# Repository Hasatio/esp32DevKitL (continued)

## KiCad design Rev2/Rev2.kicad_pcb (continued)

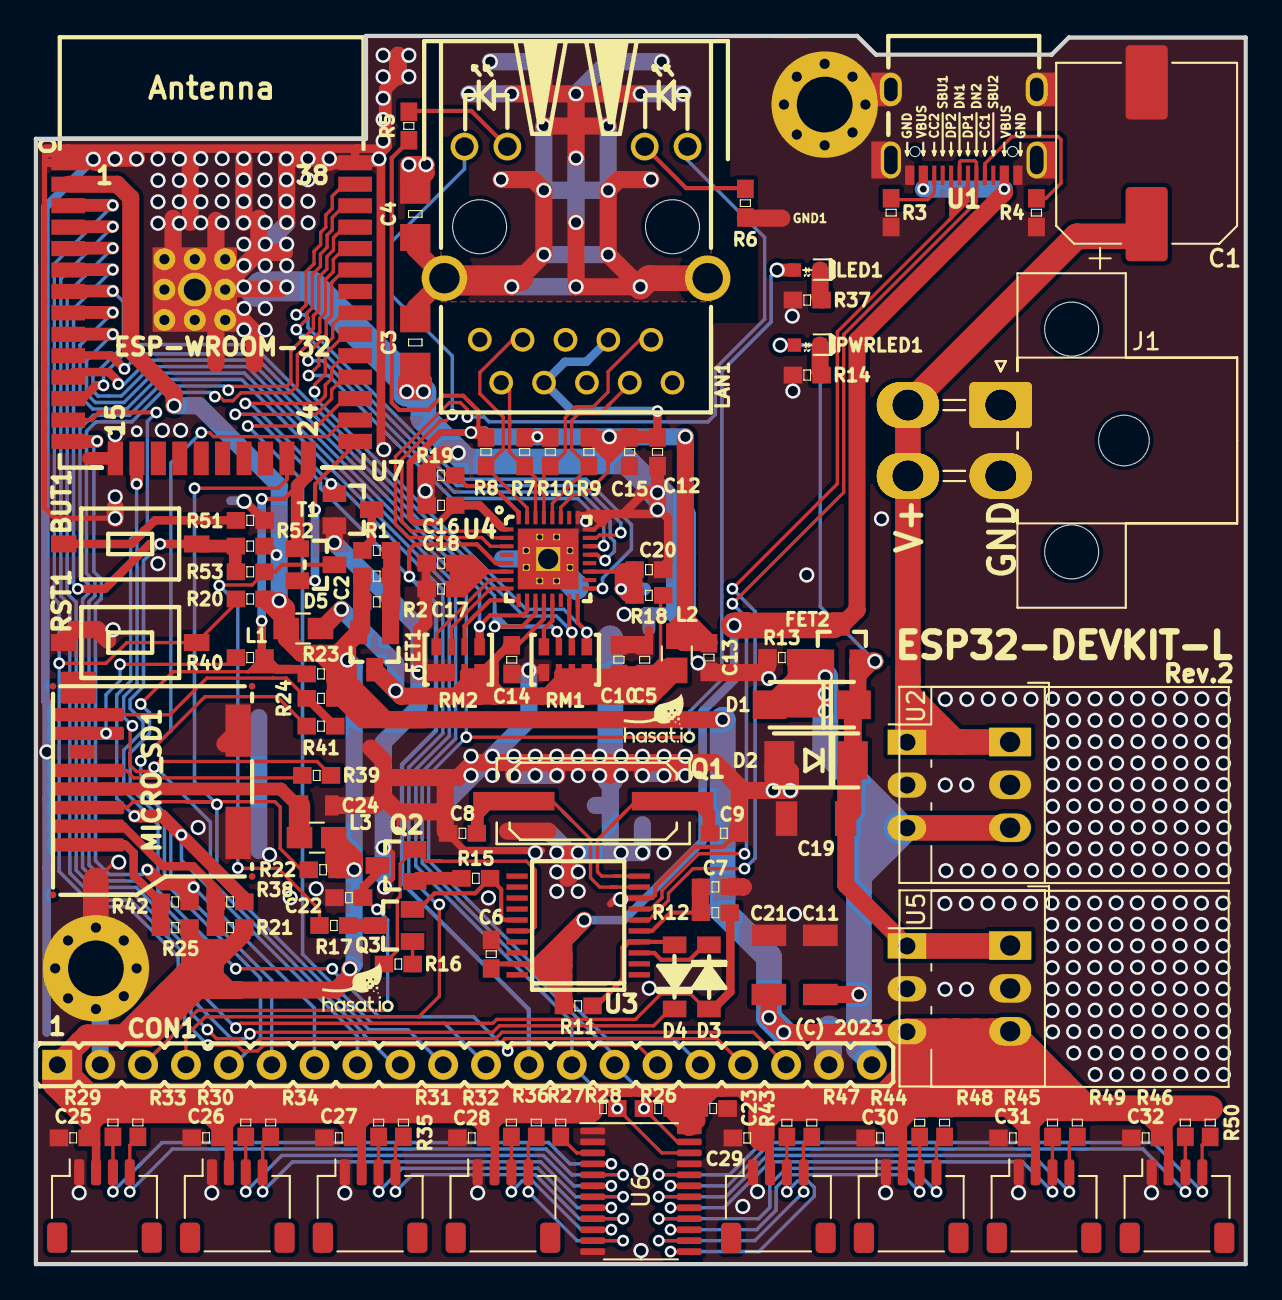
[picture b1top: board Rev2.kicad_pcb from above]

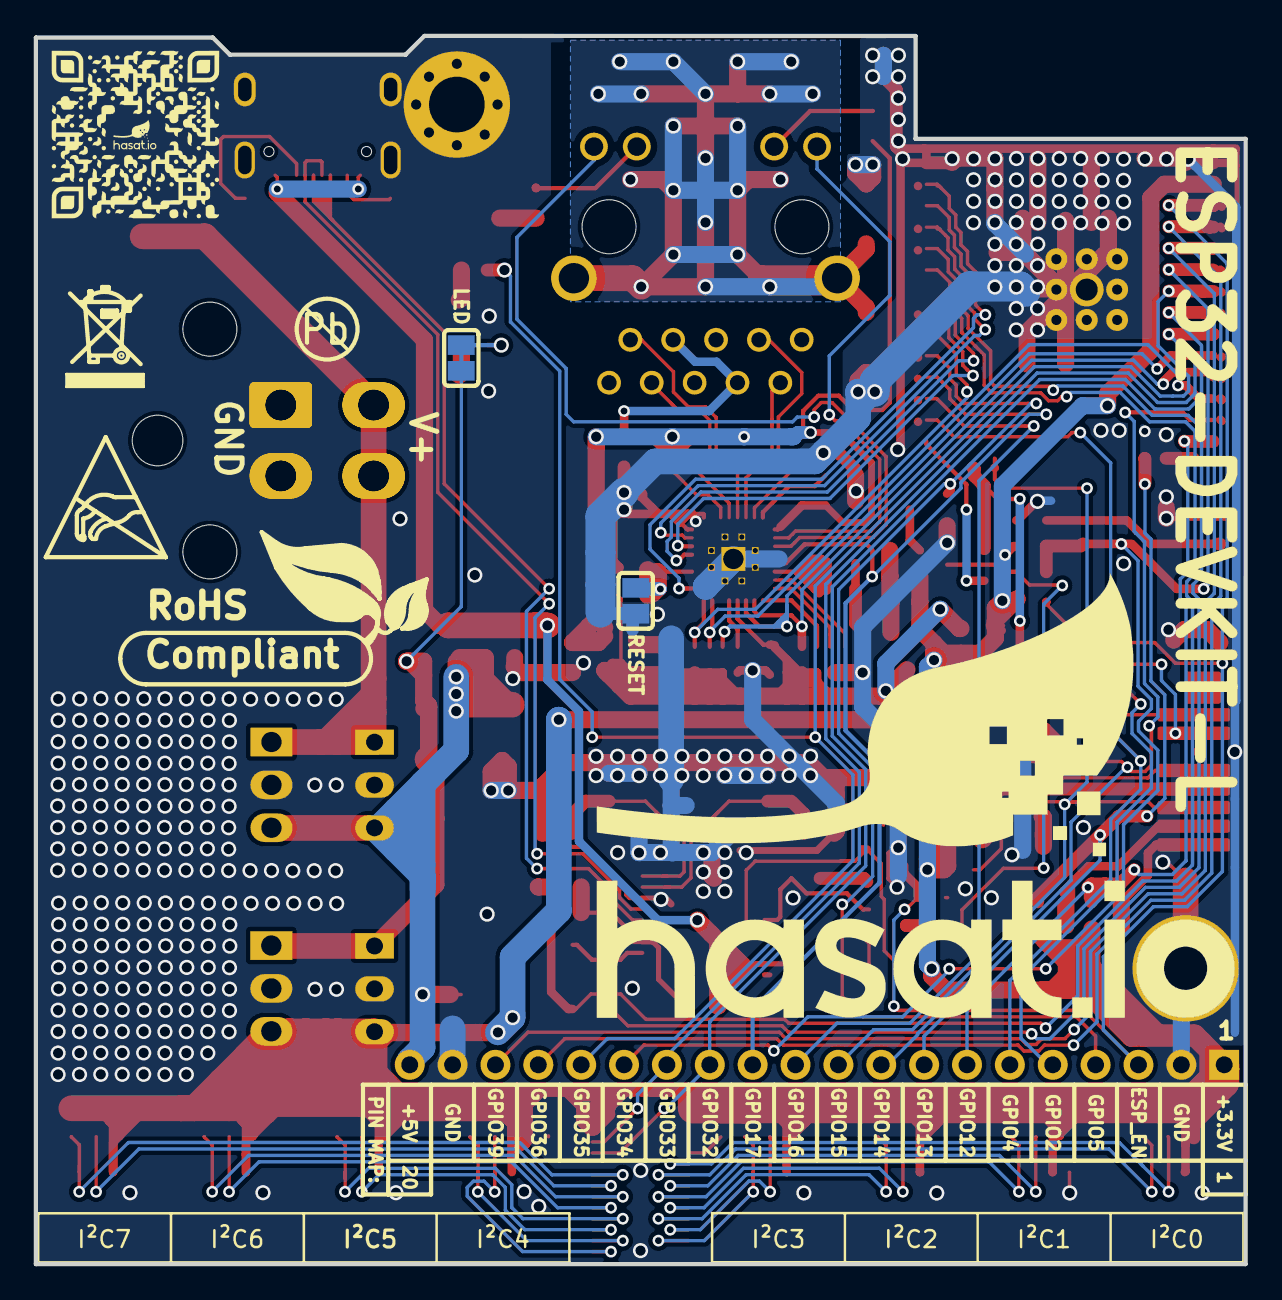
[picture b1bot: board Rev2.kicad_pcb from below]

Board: 2 copper layers, 71.7 x 72.8 mm, 133 parts (6 on the bottom side), 94 nets.

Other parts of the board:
LED: Closed; SJ
RESET: Opened; SJ
Sign-Antistatic: Val**; LOGO_ANTISTATIC_1
Sign-RecyclBin: LOGO_RECYCLEBIN_1
Sign_Pb-Free: LOGO_PBFREE
Sign_RoHS: Val**; LOGO_ROHS_1

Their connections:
+5V: LED.1, LED.2; also elsewhere on the board
GND: RESET.1; also elsewhere on the board
unnamed 91: RESET.2; also elsewhere on the board

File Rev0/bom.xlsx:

Ref | Qnty | Value | Part | Footprint | Description | Vendor
BUT1, RST1 | 2 | T1107A(6x3,8x2,5MM) | ESP32-GATEWAY_Rev_G:SIDE_WTCM-TR(3x4) | OLIMEX_Buttons-FP:T1107A(6x3,8x2,5MM)
C1 | 1 | 220uF/50V/10*10mm | Device:C_Polarized | Capacitor_SMD:CP_Elec_10x10.5 | Polarized capacitor
C2, C5, C6, C7, C13 | 5 | 22uF/6.3V/20%/X5R/C0603 | ESP32-GATEWAY_Rev_G:C | Capacitors:0603
C3 | 1 | 1nF/2000V/10%/X7R/C1206 | ESP32-GATEWAY_Rev_G:C | Capacitors:1206
C4 | 1 | NA(1nF/2000V/10%/X7R/C1206) | ESP32-GATEWAY_Rev_G:C | Capacitors:1206
C8, C12, C14, C15, C16, C18 | 6 | 100nF/50V/20%/Y5V/C0603 | ESP32-GATEWAY_Rev_G:C | Capacitors:0603
C9, C10 | 2 | 27pF/50V/5%/C0G/C0603 | ESP32-GATEWAY_Rev_G:C | Capacitors:0603
C11, C19, C21 | 3 | 330uF/6.3V/20%/X5R/C1210 | ESP32-GATEWAY_Rev_G:C | Capacitors:1210
C17 | 1 | 2.2uF/6.3V/10%/X5R/C0603 | ESP32-GATEWAY_Rev_G:C | Capacitors:0603
C20 | 1 | NA(10uF/6.3V/20%/X5R/C0603) | ESP32-GATEWAY_Rev_G:C | Capacitors:0603
C22 | 1 | 1uF/C0603 | ESP32-GATEWAY_Rev_G:C | Capacitors:0603
C23 | 1 | 100nF/6.3V/20%/X5R/C0603 | ESP32-GATEWAY_Rev_G:C | Capacitors:0603
C24 | 1 | 47uF/6.3V/20%/X5R/C0805 | ESP32-GATEWAY_Rev_G:C | Capacitors:0805
C25, C26, C27, C28, C29, C30, C31, C32 | 8 | 1uF/6.3V/20%/X5R/C0603 | ESP32-GATEWAY_Rev_G:C | Capacitors:0603
CON1 | 1 | NA(NH1x20) | ESP32-GATEWAY_Rev_G:CON20 | OLIMEX_Connectors-FP:HN1x20
D1 | 1 | 1N5822/SS34/SMA | ESP32-GATEWAY_Rev_G:D_Schottky | OLIMEX_Diodes-FP:SMA-KA
D2 | 1 | SMBJ6.0A(DO-214AA) | ESP32-GATEWAY_Rev_G:SMBJ6.0A | OLIMEX_Diodes-FP:DO214AA_1(K)-2(A)
D3, D4 | 2 | 1N5819S4/SOD123 | ESP32-GATEWAY_Rev_G:D_Schottky | OLIMEX_Diodes-FP:SOD-123_1C-2A_KA
D5 | 1 | BAT54C(SOT23-3) | ESP32-GATEWAY_Rev_G:BAT54C(SOT23-3) | OLIMEX_Diodes-FP:SOT23-3
FET1, FET2 | 2 | WPM2015-3/TR | ESP32-GATEWAY_Rev_G:P-MOS+DIOD | OLIMEX_Transistors-FP:SOT23
FID1, FID2, FID3 | 3 | Fiducial | ESP32-GATEWAY_Rev_G:Fiducial | OLIMEX_Other-FP:Fiducial1x3
GND1 | 1 | TESTPAD | ESP32-GATEWAY_Rev_G:TESTPAD | OLIMEX_Other-FP:TESTPAD_40-ROUND
I²C0, I²C1, I²C2, I²C3, I²C4, I²C5, I²C6, I²C7 | 8 | Conn_01x04_P1.00mm_Stemma qt/Qwiic | Connector_Generic:Conn_01x04 | Connector_JST:JST_SH_SM04B-SRSS-TB_1x04-1MP_P1.00mm_Horizontal | Generic connector, single row, 01x04, script generated (kicad-library-utils/sch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
J1 | 1 | Conn_02x02_P4.20mm_Molex_Horizontal | Connector_Generic:Conn_02x02_Counter_Clockwise | Connector_Molex:Molex_Mini-Fit_Jr_5569-04A1_2x02_P4.20mm_Horizontal | Generic connector, double row, 02x02, counter clockwise pin numbering scheme (s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
L1, L2, L3 | 3 | FB0805/600R/2A | ESP32-GATEWAY_Rev_G:L | OLIMEX_RLC-FP:L_0805_5MIL_DWS
LAN1 | 1 | RJLD-060TC1(LPJ4013EDNL) | ESP32-GATEWAY_Rev_G:RJLBC-060TC1_GND | OLIMEX_Connectors-FP:RJLBC-060TC1
LED1 | 1 | LED/GREEN/0603 | ESP32-GATEWAY_Rev_G:LED | OLIMEX_LEDs-FP:LED_0603_KA
LED_E1 | 1 | Closed | ESP32-GATEWAY_Rev_G:SJ | OLIMEX_Jumpers-FP:SJ
MH1, MH2 | 2 | Mounting_hole_Shield_3.3mm | ESP32-GATEWAY_Rev_G:Mounting_hole_Shield_3.3mm | OLIMEX_Other-FP:Mounting_hole_Shield_3.3mm
MICRO_SD1 | 1 | TFC-WXCP11-08-LF | ESP32-GATEWAY_Rev_G:MICRO_SD(TFC-WXCP11-08-LF) | OLIMEX_Connectors-FP:TFC-WXCP11-08-LF
PHY_RST1 | 1 | Opened | ESP32-GATEWAY_Rev_G:SJ | OLIMEX_Jumpers-FP:SJ
PWRLED1 | 1 | LED/RED/0603 | ESP32-GATEWAY_Rev_G:LED | OLIMEX_LEDs-FP:LED_0603_KA
Q1 | 1 | Q12MHz/20pF/30ppm/2P/HC-49SM(SMD) | ESP32-GATEWAY_Rev_G:Crystal | OLIMEX_Crystal-FP:Q_49U3HMS
Q2, Q3 | 2 | BC817-40(SOT23) | ESP32-GATEWAY_Rev_G:Q_NPN_BEC | OLIMEX_Transistors-FP:SOT23
R1, R15, R16 | 3 | 1k/R0603 | ESP32-GATEWAY_Rev_G:R | Resistors:0603
R2, R11, R12, R18, R20, R22, R27, R52 | 8 | 10k/R0603 | ESP32-GATEWAY_Rev_G:R | Resistors:0603
R3, R4 | 2 | 5.1k/R0603 | ESP32-C3-DevKit-Lipo_Rev_B:R | Resistors:0603
R5, R6 | 2 | 330R/R0603 | ESP32-GATEWAY_Rev_G:R | Resistors:0603
R7, R8, R9, R10 | 4 | 49.9R/1%/R0603 | ESP32-GATEWAY_Rev_G:R | Resistors:0603
R13 | 1 | 1M/R0603 | ESP32-GATEWAY_Rev_G:R | Resistors:0603
R14, R21, R23, R24, R25, R29 | 6 | 2.2k/R0603 | ESP32-GATEWAY_Rev_G:R | Resistors:0603
R17, R42, R51 | 3 | 220R/R0603 | ESP32-GATEWAY_Rev_G:R | Resistors:0603
R19 | 1 | 12.1k/1%/R0603 | ESP32-GATEWAY_Rev_G:R | Resistors:0603
R26, R28, R30, R31, R32, R33, R37, R38, R39, R40, R43, R44, R45, R46, R47, R48,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 | 18 | 4.7k/R0603 | ESP32-GATEWAY_Rev_G:R | Resistors:0603
R34, R35, R36, R53 | 4 | NA/R0603 | ESP32-GATEWAY_Rev_G:R | Resistors:0603
R41 | 1 | 10R/R0603 | ESP32-GATEWAY_Rev_G:R | Resistors:0603
RM1, RM2 | 2 | RA1206_(4X0603)_4B8_2.2k | ESP32-GATEWAY_Rev_G:RA1206_(4x0603)_4B8_Smashed | OLIMEX_RLC-FP:R_MATRIX_4
T1 | 1 | DTC114YKA | ESP32-GATEWAY_Rev_G:DTC114YKA | OLIMEX_Transistors-FP:SOT23
U1 | 1 | USB-C-16P-F(A40-00119-A52-12) | ESP32-C3-DevKit-Lipo_Rev_B:USB2.0_TYPE-C(A40-00119-A52-12) | Connector_USB:USB2.0_TYPE-C(A40-00119-A52-12)
U2 | 1 | K7805-2000R3L | Regulator_Switching:R-78B5.0-2.0 | K7812-2000R3L:K78122000R3L | 2A Step-Down DC/DC-Regulator, 6.5-32V input, 5.0V fixed Output Voltage, LM78xx 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
U3 | 1 | CH340T(SSOP20W) | ESP32-GATEWAY_Rev_G:CH340T(SSOP20W) | OLIMEX_IC-FP:SSOP-20W
U4 | 1 | LAN8710A-EZC(QFN32) | ESP32-GATEWAY_Rev_G:LAN8710A-EZC(QFN32) | OLIMEX_IC-FP:QFN32_EP(33)_5.00x5.00x0.90mm_Pitch_0.50mm
U5 | 1 | K7803-2000R3L | Regulator_Switching:R-78B3.3-2.0 | K7812-2000R3L:K78122000R3L | 2A Step-Down DC/DC-Regulator, 4.75-32V input, 3.3V fixed Output Voltage, LM78xx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
U6 | 1 | TCA9548APWR | Interface_Expansion:TCA9548APWR | Package_SO:TSSOP-24_4.4x7.8mm_P0.65mm | Low voltage 8-channel I2C switch with reset, TSSOP-24
U7 | 1 | ESP32-WROOM-32D-4MB | ESP32-GATEWAY_Rev_G:ESP-WROOM-32 | OLIMEX_Cases-FP:ESP-WROOM-32_MODULE

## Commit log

2023-03-13 13.03.23
2023-04-22 23.04.23
